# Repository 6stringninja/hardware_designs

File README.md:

hardware_designs
================

Open Hardware designs

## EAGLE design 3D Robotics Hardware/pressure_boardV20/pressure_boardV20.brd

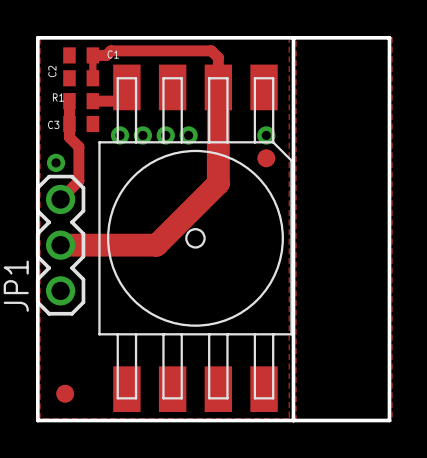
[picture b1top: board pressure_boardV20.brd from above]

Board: 2 copper layers, 19.5 x 21.3 mm, 8 parts (0 on the bottom side), 4 nets.

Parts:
C1: .1uF; C0402
C2: 1uF; C0402
C3: .33uF; C0402
JP1: 1X03
JP2, JP3: FIDUCIAL1X2; FIDUCIAL-1X2
R1: 750; C0402
U$1: MPXA6115A6U; CASE482

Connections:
GND: C1.2, C2.2, C3.2, JP1.1, U$1.3
unnamed: R1.2, U$1.4
PRESSURE: C3.1, JP1.3, R1.1
VCC: C1.1, C2.1, JP1.2, U$1.2

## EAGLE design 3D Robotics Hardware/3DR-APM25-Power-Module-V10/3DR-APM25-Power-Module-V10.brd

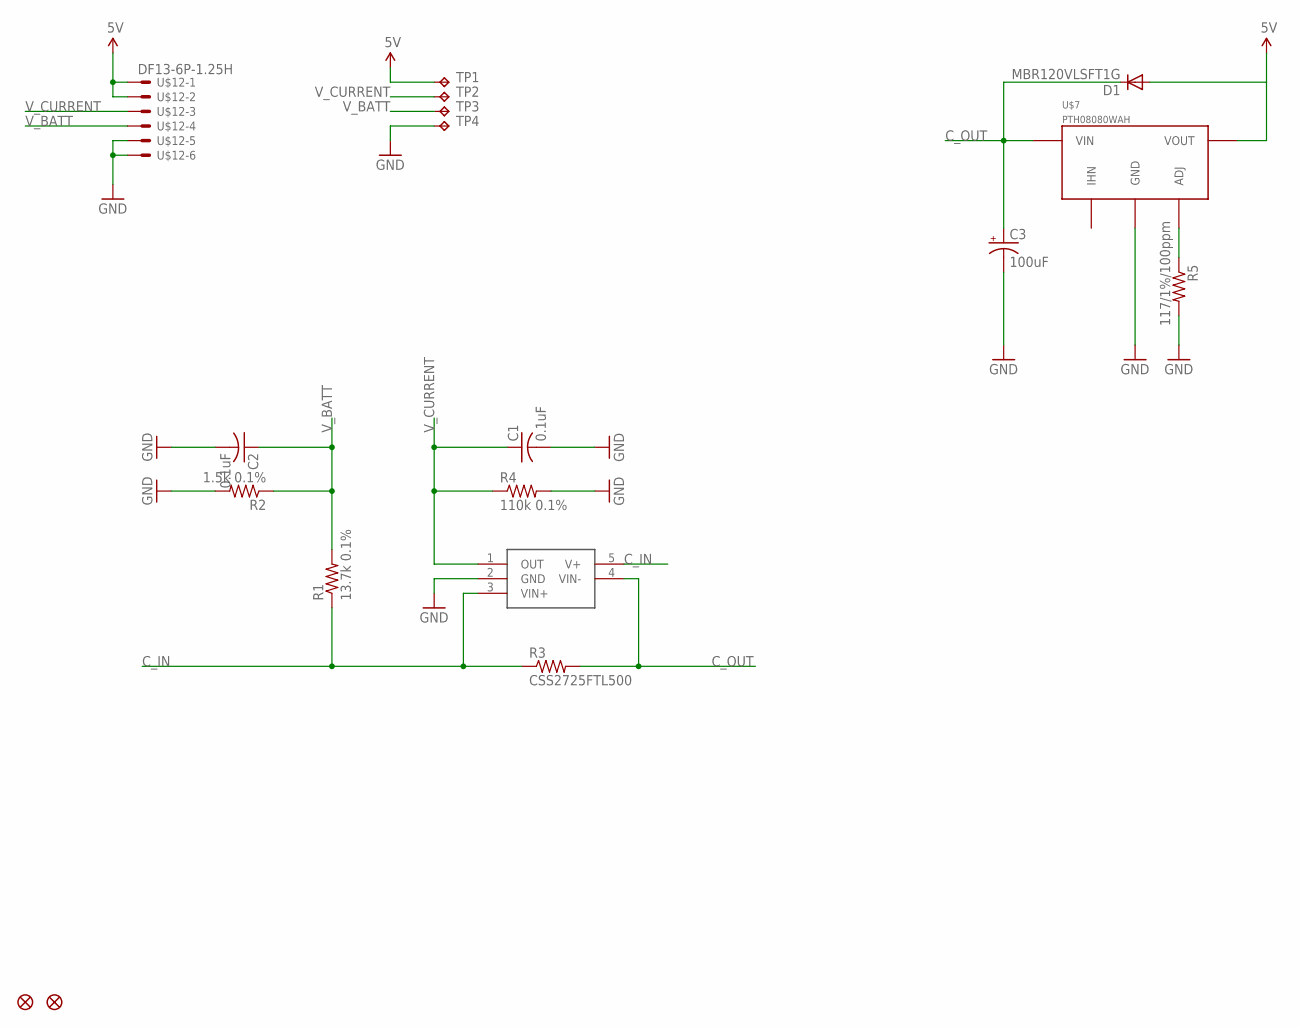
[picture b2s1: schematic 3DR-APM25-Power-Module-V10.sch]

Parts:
C1, C2: 0.1uF; C0402
C3: 100uF; EIA7343
D1: MBR120VLSFT1G; SOD-123-DIO
JP1, JP2: FIDUCIAL1X2; FIDUCIAL-1X2
R1: 13.7k 0.1%; 0402-RES
R2: 1.5k 0.1%; 0402-RES
R3: CSS2725FTL500; 2725-RES
R4: 110k 0.1%; 0402-RES
R5: 117/1%/100ppm; 0402-RES
TP1, TP2, TP3, TP4: TPTP19SQ; TP19SQ
U$2: INA169; SOT23-5
U$7: PTH08080WAH; PTH08080W_TH
U$12: DF13-6P-1.25H; DF13A-6P-1.25H

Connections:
C_IN: R1.1, R3.P$1 (1), U$2.3 (VIN+), U$2.5 (V+)
C_OUT: C3.A (+), D1.C, R3.P$2 (2), U$2.4 (VIN-), U$7.1 (VIN)
GND: C1.2, C2.2, C3.C (-), R2.2, R4.2, R5.2, TP4.TP, U$2.2 (GND), U$7.2 (GND), U$12.5, U$12.6
unnamed: R5.1, U$7.4 (ADJ)
VDD_5V: D1.A, TP1.TP, U$7.3 (VOUT), U$12.1, U$12.2
V_BATT: C2.1, R1.2, R2.1, TP3.TP, U$12.4
V_CURRENT: C1.1, R4.1, TP2.TP, U$2.1 (OUT), U$12.3

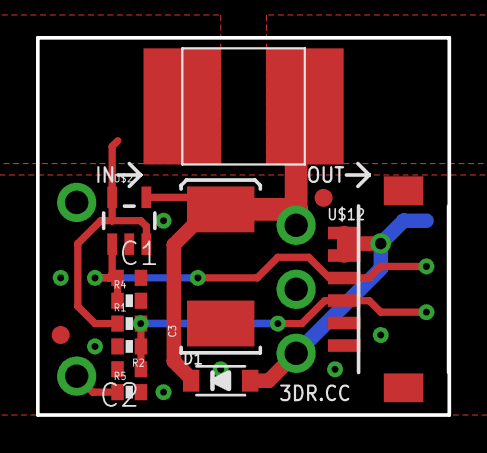
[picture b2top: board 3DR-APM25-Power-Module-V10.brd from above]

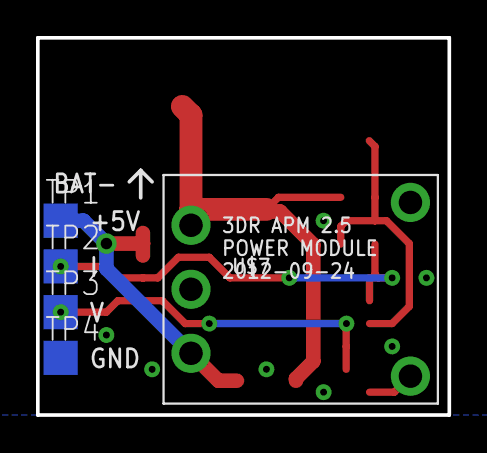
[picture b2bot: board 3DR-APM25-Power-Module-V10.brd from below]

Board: 4 copper layers, 22.9 x 21.0 mm, 18 parts (5 on the bottom side), 7 nets.

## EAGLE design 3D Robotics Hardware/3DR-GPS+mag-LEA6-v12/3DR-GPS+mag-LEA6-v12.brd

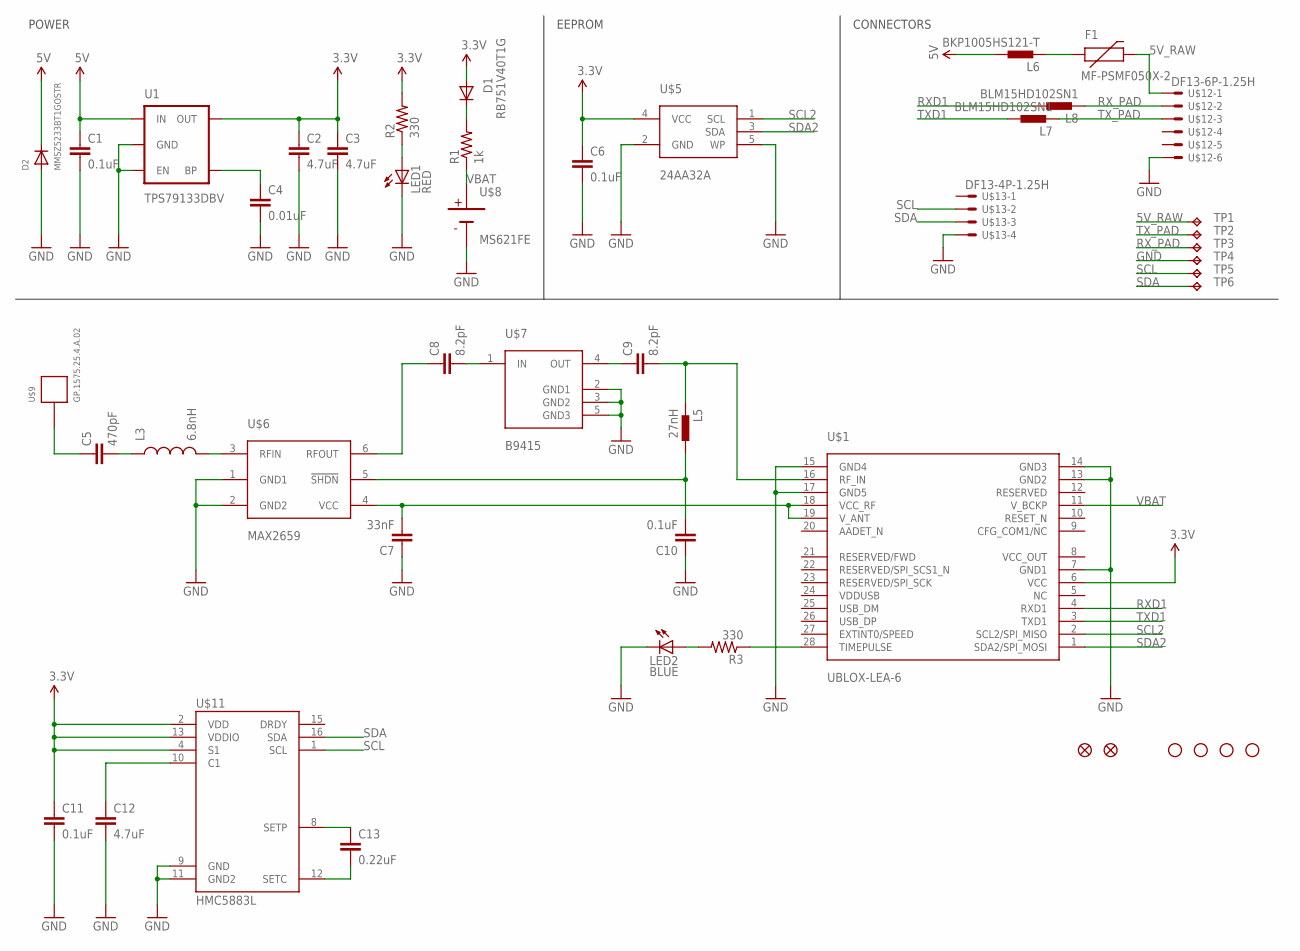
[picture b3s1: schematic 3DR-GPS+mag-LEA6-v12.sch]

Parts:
C1, C6, C10, C11: 0.1uF; 0402-CAP
C2, C3: 4.7uF; 0805
C4: 0.01uF; 0402-CAP
C5: 470pF; 0402-CAP
C7: 33nF; 0402-CAP
C8, C9: 8.2pF; 0402-CAP
C12: 4.7uF; 1206
C13: 0.22uF; 0402-CAP
D1: RB751V40T1G; SOD-323
D2: MMSZ5233BT1GOSTR; SOD-123
F1: MF-PSMF050X-2; 0805
JP1, JP2: FIDUCIAL1X2; FIDUCIAL-1X2
JP3, JP4, JP5, JP6: STAND-OFF
L3: 6.8nH; C0402
L5: 27nH; 0402-IND
L6: BKP1005HS121-T; 0402-IND
L7, L8: BLM15HD102SN1; 0402-IND
LED1: RED; LED-0603
LED2: BLUE; LED-0603
R1: 1k; 0402-RES
R2, R3: 330; 0402-RES
TP1, TP2, TP3, TP4, TP5, TP6: TPTP20SQ; TP20SQ
U1: TPS79133DBV; SOT23-5
U$1: UBLOX-LEA-6; UBLOX-LEA
U$5: 24AA32A; SOT23-5
U$6: MAX2659; UDFN-6
U$7: B9415; GPS-RF-SAW-FILTER; MFGPN B9415
U$8: MS621FE
U$9: GP.1575.25.4.A.02
U$11: HMC5883L; LPCC16
U$12: DF13-6P-1.25H; DF13A-6P-1.25H
U$13: DF13-4P-1.25H; DF13A-4P-1.25H

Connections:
3.3V: C2.1, C3.1, C6.1, C11.1, D1.2 (A), R2.2, U1.5 (OUT), U$1.6 (VCC), U$5.4 (VCC), U$11.2 (VDD), U$11.4 (S1), U$11.13 (VDDIO)
5V: C1.1, D2.C, L6.P$1 (1), U1.1 (IN)
5V_RAW: F1.2, TP1.TP, U$12.1
GND: C1.2, C2.2, C3.2, C4.2, C6.2, C7.1, C10.1, C11.2, C12.2, D2.A, LED1.C, LED2.C, TP4.TP, U1.2 (GND), U1.3 (EN), U$1.7 (GND1), U$1.13 (GND2), U$1.14 (GND3), U$1.15 (GND4), U$1.17 (GND5), U$5.2 (GND), U$5.5 (WP), U$6.1 (GND1), U$6.2 (GND2), U$7.2 (GND1), U$7.3 (GND2), U$7.5 (GND3), U$8.2 (NEG), U$11.9 (GND), U$11.11 (GND2), U$12.6, U$13.4
unnamed: L3.2, U$6.3 (RFIN)
unnamed: C4.1, U1.4 (BP)
unnamed: C5.2, L3.1
unnamed: C8.2, U$7.1 (IN)
unnamed: R3.1, U$1.28 (TIMEPULSE)
unnamed: C9.1, U$7.4 (OUT)
unnamed: C7.2, U$1.18 (VCC_RF), U$1.19 (V_ANT), U$6.4 (VCC)
unnamed: C8.1, U$6.6 (RFOUT)
unnamed: C10.2, L5.P$1 (1), U$6.5 (!SHDN)
unnamed: C5.1, U$9.1
unnamed: C9.2, L5.P$2 (2), U$1.16 (RF_IN)
unnamed: D1.1 (C), R1.2
unnamed: LED1.A, R2.1
unnamed: LED2.A, R3.2
unnamed: F1.1, L6.P$2 (2)
unnamed: C12.1, U$11.10 (C1)
unnamed: C13.1, U$11.8 (SETP)
unnamed: C13.2, U$11.12 (SETC)
RXD1: L8.P$1 (1), U$1.4 (RXD1)
RX_PAD: L8.P$2 (2), TP3.TP, U$12.2
SCL: TP5.TP, U$11.1 (SCL), U$13.2
SCL2: U$1.2 (SCL2/SPI_MISO), U$5.1 (SCL)
SDA: TP6.TP, U$11.16 (SDA), U$13.3
SDA2: U$1.1 (SDA2/SPI_MOSI), U$5.3 (SDA)
TXD1: L7.P$1 (1), U$1.3 (TXD1)
TX_PAD: L7.P$2 (2), TP2.TP, U$12.3
VBAT: R1.1, U$1.11 (V_BCKP), U$8.1 (POS)

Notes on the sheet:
POWER
EEPROM
CONNECTORS

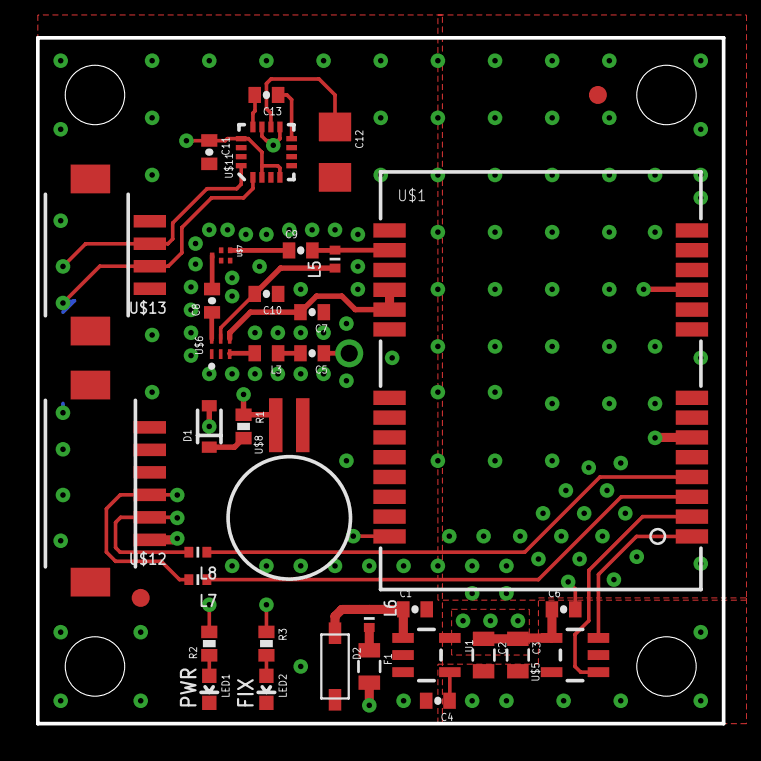
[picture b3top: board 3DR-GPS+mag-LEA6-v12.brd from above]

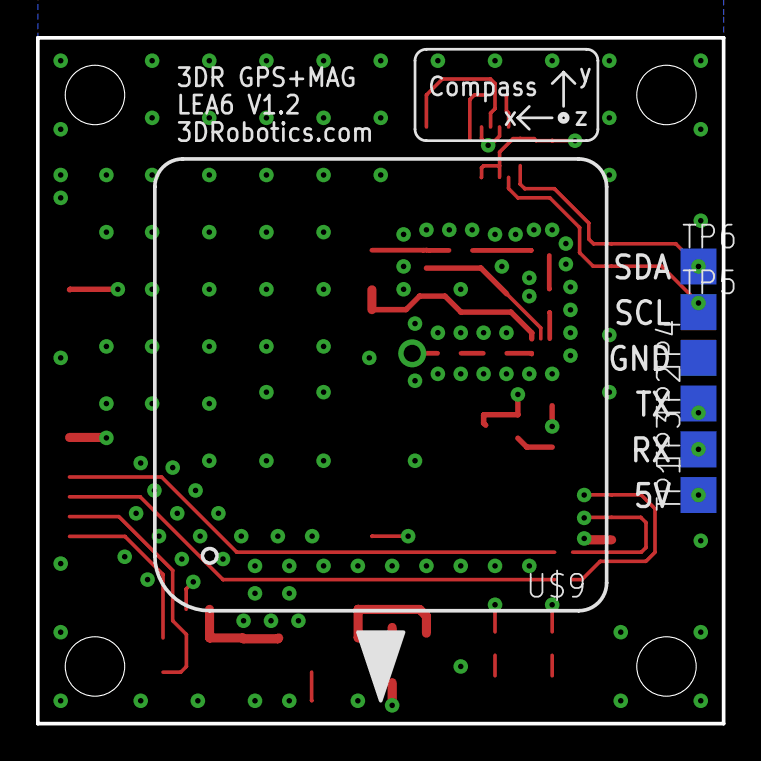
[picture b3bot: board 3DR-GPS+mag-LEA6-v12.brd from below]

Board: 4 copper layers, 38.1 x 38.1 mm, 48 parts (7 on the bottom side), 31 nets.

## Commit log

2014-08-05 Upload PX4 Hardware modules
2014-08-05 3D Robotics modules copy
    Copy of the modules sch and brd from 3DRobotics
2014-08-06 Organization of the folders
    Unzip all the files and put them into folders, in order to be easy to
    use
2014-08-08 APM design copy
    APM v1/v2/v2.6 copy
2014-08-08 Update Px4 folder
2014-08-11 add submodule Hardware (Px4 hw)
2014-09-16 Erle Telemtry
    - Small modifications in the silkscreen
    - Fabrication files creation
